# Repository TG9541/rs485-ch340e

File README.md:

# RS485-CH340E

I needed a USB-RS485 dongle with reliable automatic direction control but it was impossible to find anything that's both reliable and cheap (not to speak of small). The "budget" cmmercial USB-RS485 dongles "try" to implement direction controll with the host's Tx signal. The timing of such a solution is tricky (and potentially unreliable). A "popular" work-around is using a [questionable "dominant-recessive"](https://hackaday.io/project/167532-modbus-things-with-stm8-eforth/log/168474-finding-the-culprit) approach to RX-TX switching with a "CAN network style" recessive default state. Such a hack is certainly not RS485 compliant and may randomly fail if multiple nodes are connected, the bus cable is long, at higher bit-rates, if the weather changes, or in any combination of that.

Fortunately, the very cheap CH340E provides a true RX/TX direction signal that can be used for controlling an RS485 transceiver with perfect timing. I was surprised that there are still no cheap CH340E based RS485 dongles on the market - so I decided to make one. This repository provides a small CH340E based configurable RS485 or TTL 2/3-wire USB dongle.

If you're "shopping" for ideas how to use this solution down for a mass-market product: it's certainly possible to make solution with a minimal BOM, or one with additional robustness. Feel free to writen me an [issue](https://github.com/TG9541/rs485-ch340e/issues) if you want to learn how.

## PCB

## Schematic

The BOM is in the doc folder.

Note: the supply voltage of U1 can be selected with J3. It is either 5V (default) or 3.3V (1-2 open, 2-3 closed). This configuration option has not been tested.

## RS485 configuration:

The built-in CH340E 3.3V LDO can provide a 3.3V supply for the RS485 transceiver which makes populating the linear voltage regulator U3 (XC6206P332MR) optional. For most applications it's better to populate U3 since the maximum number of RS485 nodes that can be connected to the bus might be limited by the current that the internal LDO can provide.

Note: SW1 controlls "TX-RX echo" (pin1-1 closed) or "no echo" (pin2-3 closed, this is standard RS485 functionality). If switching isn't required the pads can be bridged with a bit of solder. Most people won't need switching and in a re-design I would certainly replace SW1 with a jumper.

### Core RS485 configuration (limited fan-out): 
Populate the following:
* front side: U1, U2, C2, C4, J2
* back side: SW1

## Standar RS485 configuration (standard fan-out):
Populate the following:
* front side: U1, U2, U3, C1, C2, C4, J2
* back side: SW1, R1, R2, D2, D3

## RS232-TTL configuration:

The dongle can be configured for 3-wire (full duplex) or 2-wire (half duplex) communication. The 2-wire option can be used for command-response console protocols, e.g., the [half-duplex STM8 eForth configuration](https://github.com/TG9541/stm8ef/wiki/STM8-eForth-Programming-Tools#using-a-serial-interface-for-2-wire-communication).

### 3-wire configuration: 
Populate the following:
* front side: U1, C2, C4, J2
* back side: (optional) R1, R2, D2, D3 

Close jumpers J1 (RX, J2.3) and J2 (TX, J2.2) on the back side. 

### 2-wire configuration: 
Populate the following:
* front side: U1, C2, C4, J2
* back side: D1, (optional) R1, R2, D2, D3 

Close jumpers J1 (RX/TX, J2.3) on the back side.

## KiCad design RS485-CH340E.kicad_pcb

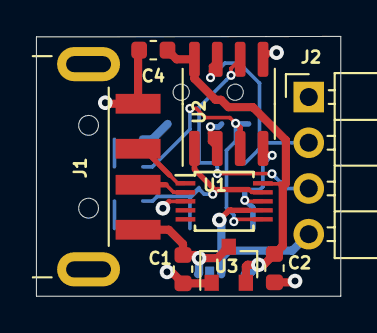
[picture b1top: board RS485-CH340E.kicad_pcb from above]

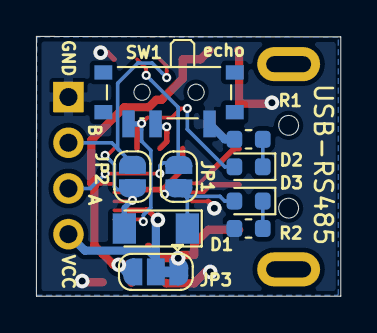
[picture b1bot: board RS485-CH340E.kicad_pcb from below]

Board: 2 copper layers, 16.9 x 14.4 mm, 17 parts (9 on the bottom side), 14 nets.

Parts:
C1, C2: 1uF; C_0603_1608Metric
C4: 100nF; C_0603_1608Metric
D1: DIODE; D_MiniMELF
D2: LED red; LED_0603_1608Metric
D3: LED green; LED_0603_1608Metric
J1: USB_A; USB_A_CNCTech_1001-011-01101_Horizontal
J2: Conn_01x04_Male; PinHeader_1x04_P2.54mm_Horizontal
JP1: RX; SolderJumper-2_P1.3mm_Open_RoundedPad1.0x1.5mm
JP2: TX; SolderJumper-2_P1.3mm_Open_RoundedPad1.0x1.5mm
JP3: SolderJumper_3_Bridged12; SolderJumper-3_P1.3mm_Bridged12_RoundedPad1.0x1.5mm
R1, R2: 4k7; R_0603_1608Metric
SW1: SW_SPDT; SW_SPDT_PCM12
U1: CH340E; TSSOP-10_3x3mm_P0.5mm
U2: SP3485CN; SOIC-8_3.9x4.9mm_P1.27mm
U3: XC6206P332MR; SOT-23

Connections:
+3V3: C2.1, C4.1, JP3.3, U1.10, U2.8, U3.2
/RxD: D1.1, D3.2, JP1.1, U1.9, U2.1
/TxD: D1.2, JP2.1, U1.8, U2.4
GND: C1.2, C2.2, C4.2, J1.4, J2.1, R1.2, R2.2, SW1.1, U1.3, U2.5, U3.1
unnamed: D2.1, R1.1
unnamed: D2.2, SW1.3, U1.6, U2.3
unnamed: D3.1, R2.1
unnamed: J1.2, U1.2
unnamed: J1.3, U1.1
unnamed: J2.2, JP2.2, U2.7
unnamed: J2.3, JP1.2, U2.6
unnamed: SW1.2, U2.2
VBUS: C1.1, J1.1, JP3.1, U3.3
VCC: J2.4, JP3.2, U1.7

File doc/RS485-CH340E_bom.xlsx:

Source: | /home/thomas/kicad/rs485-ch340e/RS485-CH340E.sch
Date: | Di 05 Nov 2019 20:26:29 CET
Tool: | Eeschema 5.1.4-e60b266~84~ubuntu16.04.1
Generator: | /usr/share/kicad/plugins/bom_csv_grouped_by_value_with_fp.py
Component Count: | 17
Ref | Qnty | Value | Cmp name | Footprint | Description | Vendor
C2, C1, | 2 | 1uF | C | Capacitor_SMD:C_0603_1608Metric | Unpolarized capacitor
C4, | 1 | 100nF | C | Capacitor_SMD:C_0603_1608Metric | Unpolarized capacitor
D1, | 1 | 1N4148 MiniMELF (optional) | DIODE | Diode_SMD:D_MiniMELF | Diode symbol for simulation only. Pin order incompatible with official kicad fo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
D2, | 1 | LED red | LED | LED_SMD:LED_0603_1608Metric | Light emitting diode
D3, | 1 | LED green | LED | LED_SMD:LED_0603_1608Metric | Light emitting diode
J1, | 1 | USB_A | USB_A | Connector_USB:USB_A_CNCTech_1001-011-01101_Horizontal | USB Type A connector
J2, | 1 | Conn_01x04_Male | Conn_01x04_Male | Connector_PinHeader_2.54mm:PinHeader_1x04_P2.54mm_Horizontal | Generic connector, single row, 01x04, script generated (kicad-library-utils/sch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
JP1, | 1 | RX | SolderJumper_2_Open | Jumper:SolderJumper-2_P1.3mm_Open_RoundedPad1.0x1.5mm | Solder Jumper, 2-pole, open
JP2, | 1 | TX | SolderJumper_2_Open | Jumper:SolderJumper-2_P1.3mm_Open_RoundedPad1.0x1.5mm | Solder Jumper, 2-pole, open
JP3, | 1 | SolderJumper_3_Bridged12 | SolderJumper_3_Bridged12 | Jumper:SolderJumper-3_P1.3mm_Bridged12_RoundedPad1.0x1.5mm | 3-pole Solder Jumper, pins 1+2 closed/bridged
R2, R1, | 2 | 4k7 | R | Resistor_SMD:R_0603_1608Metric | Resistor
SW1, | 1 | MSK-12C02 | SW_SPDT | Button_Switch_SMD:SW_SPDT_PCM12 | Switch, single pole double throw
U1, | 1 | CH340E | CH340E | Package_SO:TSSOP-10_3x3mm_P0.5mm
U2, | 1 | SP3485CN (optional) | SP3485CN | Package_SO:SOIC-8_3.9x4.9mm_P1.27mm | 3.3V Low Power Half-Duplex RS-485 Transceiver 10Mbps, SO8
U3, | 1 | XC6206P332MR | XC6206P332MR | Package_TO_SOT_SMD:SOT-23 | Low Quiescent Current LDO Regulator, 3.3V, 200 mA, Vin<=7V, SOT-23
